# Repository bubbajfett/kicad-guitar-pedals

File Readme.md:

# Current guitar pedal projects 

Current count of pedals in this repo is something like 50.    Not doing too many more, though I have a FV-1 and a Daisy seed one I'm working on longer term, as well as clearing out the box of shame.  I have been stymied on a number of recent pedal builds testing out of box due to the rig I was using having some kind of bad wires, causing huge amounts of hum.    I reworked the testing rig and have now verified about 6 or 7 more in last week.

Anyway, the requirements here are KICAD 7 or later.     Each subdir has a gerbers directory, which has the final set of gerbers used.    

The latest change is to add a PDF in the root of each pedal directory, which has the readme, the schematic as an image, and the front and back layout of the PCB (F.Cu+F.Silkscreen, B.Cu+F.Silkscreen). Also a BOM of the parts is included.    This was all done scripted using kicad-cli  in a VM (Fedora 44, Kicad 10 !!!) as the Kicad 7 versions of this did not work very well.   I will add pics of the real tested boards as an addendum to these.    This change was a result of some feedback I recieved about the lack of clarity of what is in this repo.

These pedals have been a learning exercise for me in KiCad. Any guitar pedal PCB published here has been built and tested. In some cases, more than two versions of boards have been created.   The worst case was 5 versions.

The main idea for doing my own PCB is to allow me to change the footprints and merge and/or hack pedal schematics to come up with new ideas.
The other reason is I am redoing my pedalboard to convert from side-jacks/veroboard layout to  top-jacks/pcbs.   I have gotten to dislike veroboard layouts.

I am an amateur in this.   Also this has been a huge learning exercise.    I've tried to be consistent with some design decisions.

*   back of board mounted POTs.   Tried using both 16mm and 9mm pots (RK97?)
*   common format pinheader so to be able to use 4pin dupont connector or JST connector when building.   The topjacks pcb broke this "common format (9v, Out, In, Gnd --- from left to right)",
in that it was initially intended that the PCB be oriented closest to the the 125B shell bottom, but that made assembly more difficult.   I ordered panels of it from JLPCB, and so I;m just wiring them
backwards.
*   power on the top jack connector, with diode protection there.
*   led on the stomp switch
*   125B form factor.    Top jacks in a 1590B is really hard unless the power connector is modified or moved somewhere else.

One thing I have learned is that the text size on some of these boards is below
the JLPCB minimum recommended size; the text looks fine in osh-park boards.

Several of the build docs have pictures of the final builds.    Tonemachine is the latest...

Putting these pedal layouts out there for any interested party.   Do what you want with them. 

Here are the current repo contents.   These have all been tested outside the box,
and multiple have been successfully boxed.  12  have been boxed and are 
now on the pedalboard. 

| PEDAL | BUILD DOC | Verified|
| ----  | -------   | ------- |
| Delay/deep_blue_delay | [deep-blue-delay](./Delay/deep_blue_delay/deep_blue_delay.pdf) | Y |
| Util/stomp-chargepump |  [stomp-chargepump](./Util/stomp-chargepump/stomp-chargepump.pdf) | Y |
| Util/stomp-3pdt | [stomp-3pdt](./Util/stomp-3pdt/stomp-3pdt.pdf) | Y | 
| Util/top-jacks | [top-jacks](./Util/top-jacks/top-jacks.pdf) | Y |
| Distortion/900fuzz | [900fuzz](./Distortion/900fuzz/900fuzz.pdf) | Y |
| Distortion/acapulcogold | [acapulcogold](./Distortion/acapulcogold/acapulcogold.pdf) | Y |
| Distortion/bigmuff | [bigmuff](./Distortion/bigmuff/bigmuff.pdf) | Y | 
| Distortion/bigmuff/bmp-ramshead  | --- | Y |
| Distortion/blackdarling | --- | Y |
| Distortion/brutalistjr | [brutalist jr](./Distortion/brutalistjr/brutalistjr.pdf) | Y |
| Distortion/bmp2 | [BMP2](./Distortion/bmp2/bmp2.pdf) | Y |
| Distortion/ejfuzzface | [ejfuzzface](./Distortion/ejfuzzface/ejfuzzface.pdf) | Y |
| Distortion/fortinfuzz | [fortinfuzz](./Distortion/fortinfuzz/fortinfuzz.pdf) | Y |
| Distortion/fuzzface | [fuzzface](./Distortion/fuzzface/fuzzface.pdf) | Y |
| Distortion/fy2 | [Shin-ey fy2](./Distortion/fy2/fy2.pdf) | Y  |
| Distortion/lizardq | [lizardq](./Distortion/lizardq/lizardq.pdf) | Y | 
| Distortion/percolator | [percolator](./Distortion/percolator/percolator.pdf) | Y |
| Distortion/tonemachine | [tonemachine](./Distortion/tonemachine/tonemachine.pdf) | Y |
| Distortion/redllama | [redllama](./Distortion/redllama/redllama.pdf) | Y |
| Distortion/whitefuzz | [whitefuzz](./Distortion/whitefuzz/whitefuzz.pdf) | Y |
| Compressor/bearhug | [bearhug](./Compressor/bearhug/bearhug.pdf) | Y | 
| Compressor/engineers_thumb | [engineers_thumb](./Compressor/engineers_thumb/engineers_thumb.pdf) | Y |
| Compressor/dynacomp | ---  | Maybe? |
| Compressor/dynacomp-lm13700  | --- | N |
| Chorus/littleangel | [littleangel](./Chorus/littleangel/littleangel.pdf) | Y |
| Envelope/mutron | [mutron-v](./Envelope/mutron/mutron.pdf) | Y |
| Overdrive/SFTii | [sftii](./Overdrive/SFTii/SFTii.pdf) | Y | 
| Overdrive/triple_wreck | [triple_wreck](./Overdrive/triple_wreck/triple_wreck.pdf) | Y | 
| Overdrive/ecstacy | [ecstacy](./Overdrive/ecstacy/ecstacy.pdf) | Y | 
| Overdrive/badmonkey | [badmonkey](./Overdrive/badmonkey/badmonkey.pdf) | Y |
| Overdrive/bsiab |  [bsiab](./Overdrive/bsiab/bsiab.pdf) | Y |
| Overdrive/fatdrive | [fatdrive](./Overdrive/fatdrive/fatdrive.pdf)| Y |
| Overdrive/tweed57 | [tweed57](./Overdrive/tweed57/tweed57.pdf)|Y|
| Overdrive/timmy  | [timmy](./Overdrive/timmy/timmy.pdf) | Y |
| Overdrive/KoT | [KoT](./Overdrive/KoT/KoT.pdf) | Y | 
| Overdrive/ocd | [ocd](./Overdrive/ocd/ocd.pdf) | Y |
| Overdrive/revv-g4 | [revv-g4](./Overdrive/revv-g4/revv-g4.pdf) | Y |
| Overdrive/drboogie | ... | Y |
| Overdrive/umble | [umble](./Overdrive/umble/umble.pdf) | Y |
| Equalizer/eq | [eq](./Equalizer/eq/eq.pdf) | Y | 

PCB builds in progress are

*   Barbershop (redo)
*   paisley
*   plexidrive
*   beod

*   Klon
*   phase45
*   g2
*   bluesdriver
*   katzenkonig
*   sabbracadabra
*   tubescreamer

And 4 are stuck in the box of shame 
*   zombiechorus (9 months non-working...)
*   causalty4 phaser  (ugggh ... so close)
*   box of metal      
*   kraken

All the above subprojects have a gerbers/ subdir with the last gerber file I generated. Using OshPark for pcb generation.    They were done with Kicad 7.
Most were done with manual placement of the elements on the PCB, and then using freerouting to autoroute the traces.

License is the general Creative Commons.     Have fun!

All registered trademarks are owned by their respective owners.

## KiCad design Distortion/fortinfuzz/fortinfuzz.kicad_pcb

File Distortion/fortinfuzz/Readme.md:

# Fortin Fuzz

This is a clone of the Fortin Fuzz by fortin Amps.

The Fortin Fuzz has a very heavy doom, sludge, and drone tones.

The schematic is based on the 410 Fuzz by Pedal PCB.

All trademarks belong to their respective owners.

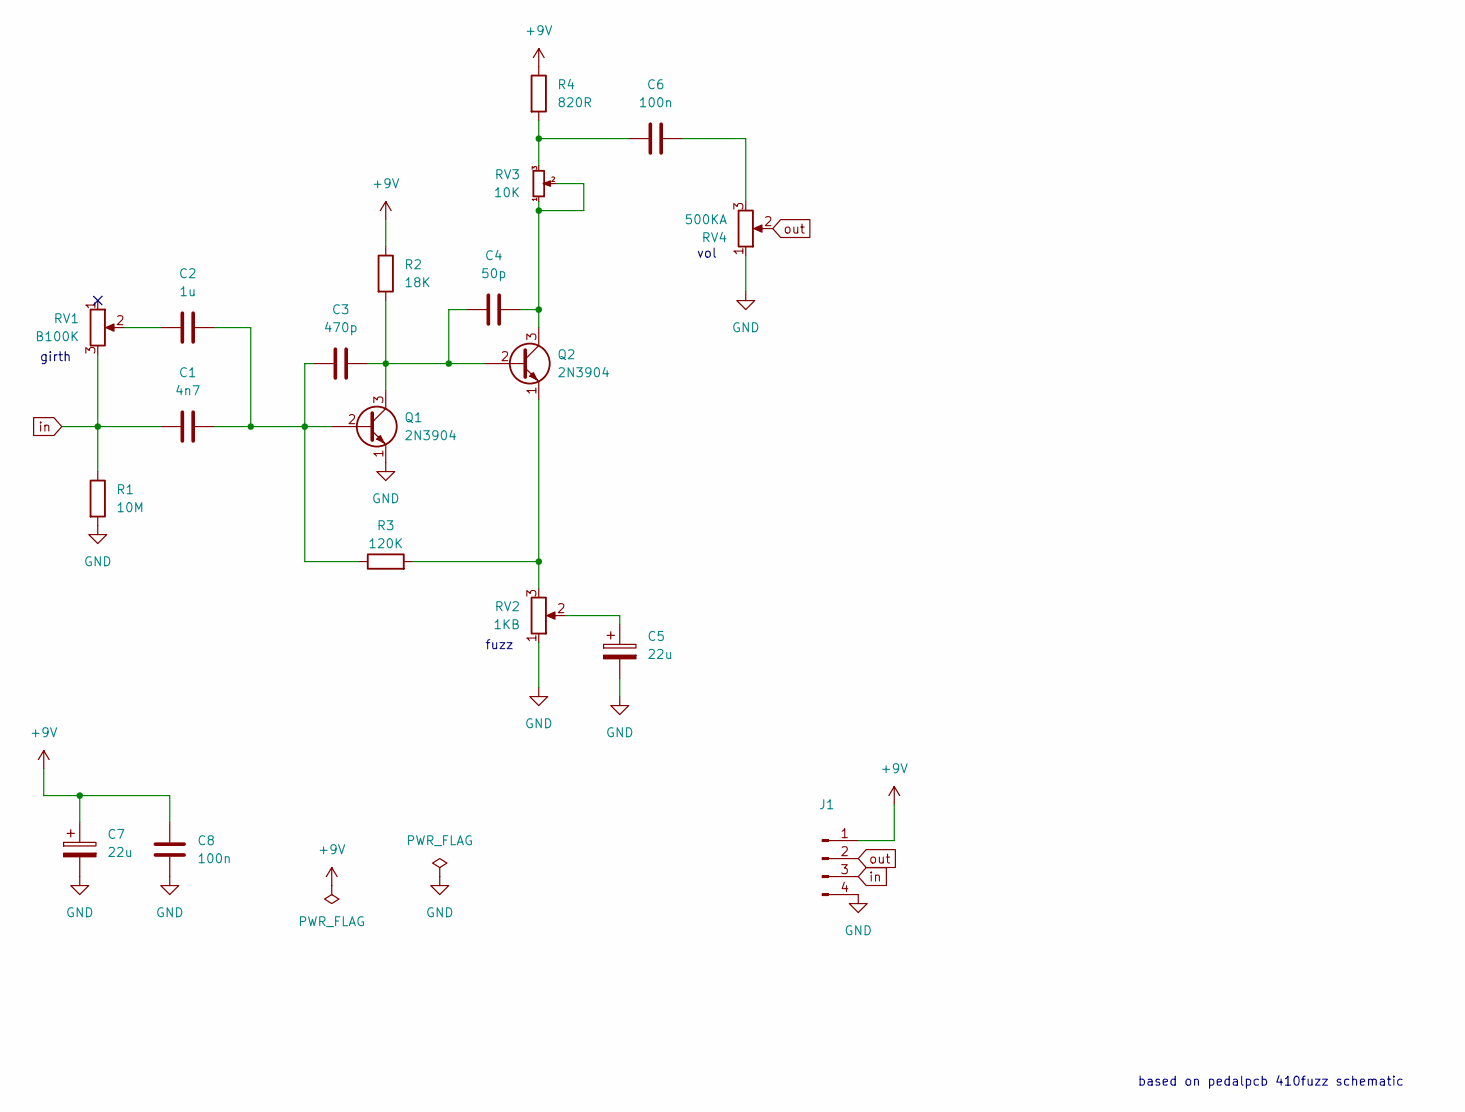
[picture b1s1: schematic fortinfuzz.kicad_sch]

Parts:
C1: 4n7; C_Rect_L7.0mm_W2.0mm_P5.00mm
C2: 1u; C_Rect_L7.0mm_W3.5mm_P5.00mm
C3: 470p; C_Rect_L7.0mm_W2.0mm_P5.00mm
C4: 50p; C_Rect_L7.0mm_W2.0mm_P5.00mm
C5, C7: 22u; CP_Radial_D5.0mm_P2.00mm
C6: 100n; C_Rect_L7.0mm_W3.5mm_P5.00mm
C8: 100n; C_Rect_L7.0mm_W2.5mm_P5.00mm
J1: Conn_01x04_Pin; PinSocket_1x04_P2.54mm_Vertical
Q1, Q2: 2N3904; TO-92_Inline
R1: 10M; R_Axial_DIN0207_L6.3mm_D2.5mm_P10.16mm_Horizontal
R2: 18K; R_Axial_DIN0207_L6.3mm_D2.5mm_P10.16mm_Horizontal
R3: 120K; R_Axial_DIN0207_L6.3mm_D2.5mm_P10.16mm_Horizontal
R4: 820R; R_Axial_DIN0207_L6.3mm_D2.5mm_P10.16mm_Horizontal
RV1: B100K; Pot_Underside
RV2: 1KB; Pot_Underside
RV3: 10K; Potentiometer_Runtron_RM-065_Vertical
RV4: 500KA; Pot_Underside

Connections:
+9V: C7.1, C8.2, J1.1, R2.1, R4.1
GND: C5.2, C7.2, C8.1, J1.4, Q1.1 (E), R1.2, RV2.1, RV4.1
unnamed: C2.1, RV1.2
unnamed: C5.1, RV2.2
unnamed: C6.1, R4.2, RV3.3
unnamed: C6.2, RV4.3
unnamed: C1.2, C2.2, C3.1, Q1.2 (B), R3.1
unnamed: C3.2, C4.1, Q1.3 (C), Q2.2 (B), R2.2
unnamed: C4.2, Q2.3 (C), RV3.1, RV3.2
unnamed: Q2.1 (E), R3.2, RV2.3
in: C1.1, J1.3, R1.1, RV1.3
out: J1.2, RV4.2

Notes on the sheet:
based on pedalpcb 410fuzz schematic
girth
fuzz
vol

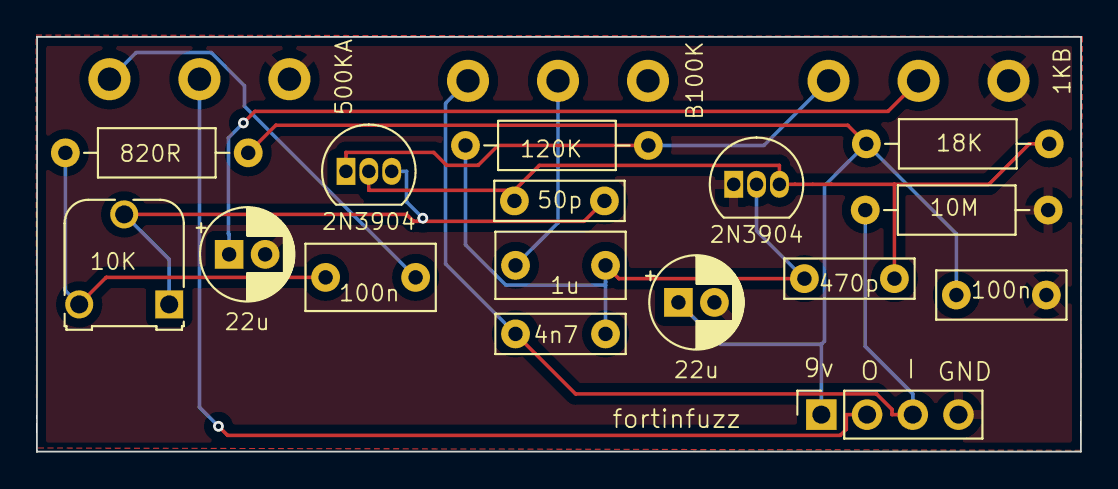
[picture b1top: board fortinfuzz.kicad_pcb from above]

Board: 2 copper layers, 58.0 x 23.0 mm, 19 parts (0 on the bottom side), 12 nets.

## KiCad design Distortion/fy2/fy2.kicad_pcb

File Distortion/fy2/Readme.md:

# Shin-ei Companion FY-2

This is a clone of the FY2 pedal, which is a very old fuzz pedal.
This produces a very thick sound. 

So this pedal circuit  is verified.  I hate using a 125B box on something
this small but my last attempt at boxing top-jacks on a
1590B did not work very well.

Anyway, all trademarks belong to their respective owners.

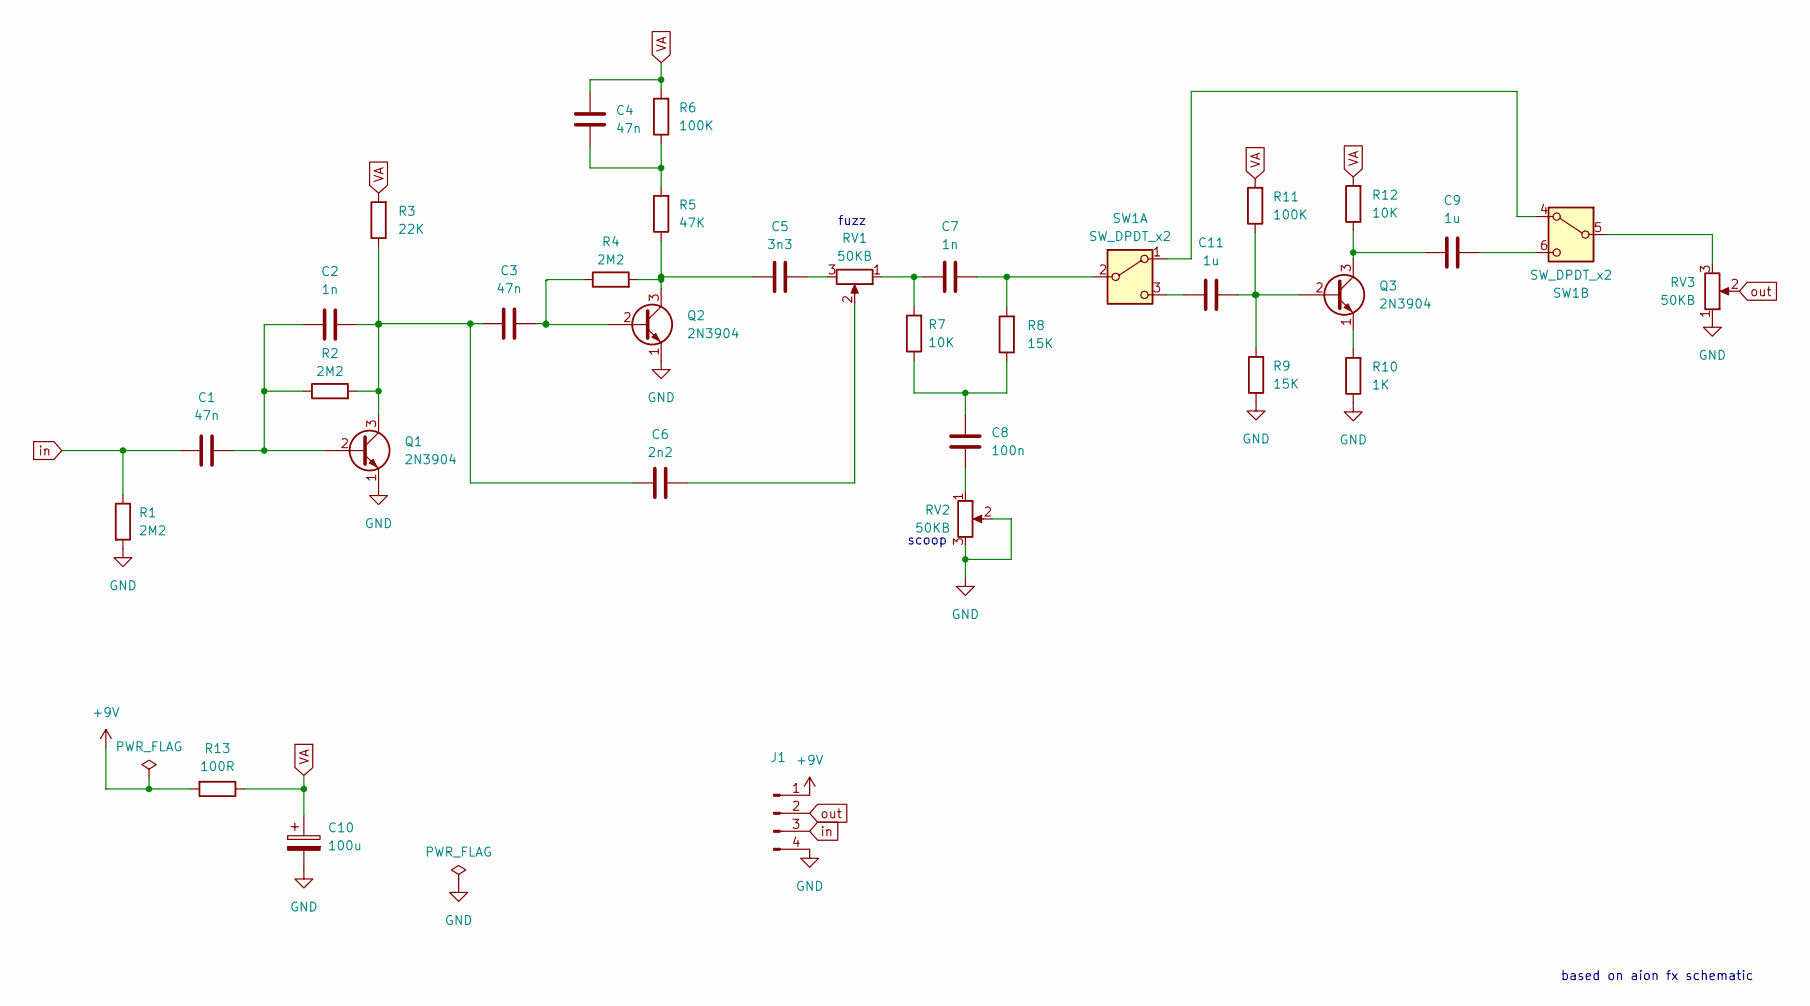
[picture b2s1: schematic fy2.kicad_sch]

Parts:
C1, C3, C4: 47n; C_Rect_L7.0mm_W2.0mm_P5.00mm
C2, C7: 1n; C_Rect_L7.0mm_W2.0mm_P5.00mm
C5: 3n3; C_Rect_L7.0mm_W2.0mm_P5.00mm
C6: 2n2; C_Rect_L7.0mm_W2.0mm_P5.00mm
C8: 100n; C_Rect_L7.0mm_W2.0mm_P5.00mm
C9, C11: 1u; C_Rect_L7.0mm_W3.5mm_P5.00mm
C10: 100u; CP_Radial_D7.5mm_P2.50mm
J1: Conn_01x04_Pin; PinSocket_1x04_P2.54mm_Vertical
Q1, Q2, Q3: 2N3904; TO-92_Inline
R1, R2, R4: 2M2; R_Axial_DIN0207_L6.3mm_D2.5mm_P10.16mm_Horizontal
R3: 22K; R_Axial_DIN0207_L6.3mm_D2.5mm_P10.16mm_Horizontal
R5: 47K; R_Axial_DIN0207_L6.3mm_D2.5mm_P10.16mm_Horizontal
R6, R11: 100K; R_Axial_DIN0207_L6.3mm_D2.5mm_P10.16mm_Horizontal
R7, R12: 10K; R_Axial_DIN0207_L6.3mm_D2.5mm_P10.16mm_Horizontal
R8, R9: 15K; R_Axial_DIN0207_L6.3mm_D2.5mm_P10.16mm_Horizontal
R10: 1K; R_Axial_DIN0207_L6.3mm_D2.5mm_P10.16mm_Horizontal
R13: 100R; R_Axial_DIN0207_L6.3mm_D2.5mm_P10.16mm_Horizontal
RV1, RV2, RV3: 50KB; Pot_Underside
SW1: SW_DPDT_x2; SWITCH-M1-DPDT

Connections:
+9V: J1.1, R13.2
GND: C10.2, J1.4, Q1.1 (E), Q2.1 (E), R1.2, R9.1, R10.1, RV2.2, RV2.3, RV3.1
unnamed: C4.1, R5.2, R6.1
unnamed: C5.2, RV1.3
unnamed: C6.2, RV1.2
unnamed: C7.1, R7.2, RV1.1
unnamed: C8.1, RV2.1
unnamed: C8.2, R7.1, R8.1
unnamed: C1.2, C2.1, Q1.2 (B), R2.1
unnamed: C2.2, C3.1, C6.1, Q1.3 (C), R2.2, R3.1
unnamed: C3.2, Q2.2 (B), R4.1
unnamed: C5.1, Q2.3 (C), R4.2, R5.1
unnamed: C11.2, Q3.2 (B), R9.2, R11.1
unnamed: C9.1, Q3.3 (C), R12.1
unnamed: Q3.1 (E), R10.2
unnamed: SW1.1 (A), SW1.4 (A)
unnamed: C7.2, R8.2, SW1.2 (B)
unnamed: C11.1, SW1.3 (C)
unnamed: RV3.3, SW1.5 (B)
unnamed: C9.2, SW1.6 (C)
VA: C4.2, C10.1, R3.2, R6.2, R11.2, R12.2, R13.1
in: C1.1, J1.3, R1.1
out: J1.2, RV3.2

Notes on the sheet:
scoop
fuzz
based on aion fx schematic

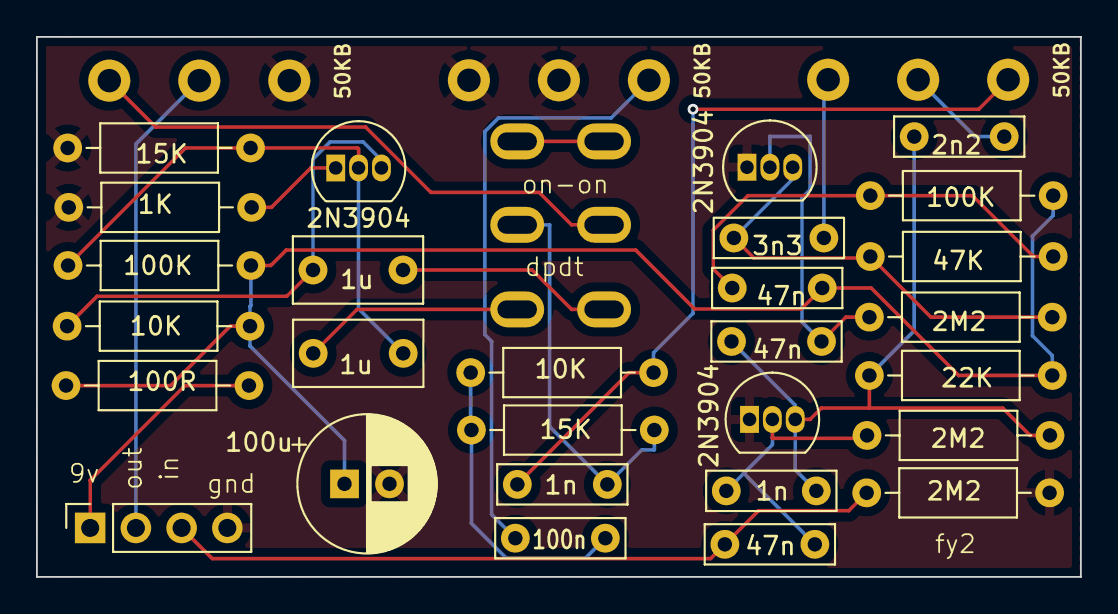
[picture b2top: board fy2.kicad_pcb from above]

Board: 2 copper layers, 58.0 x 30.0 mm, 32 parts (0 on the bottom side), 23 nets.

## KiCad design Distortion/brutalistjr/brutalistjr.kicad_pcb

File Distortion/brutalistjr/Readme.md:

# brutalist jr

This is a clone of the Brutalist JR by GOd CIty Instruments.

A very very nice distortion.   This will definitely get boxed up.

All trademarks belong to their respective owners.

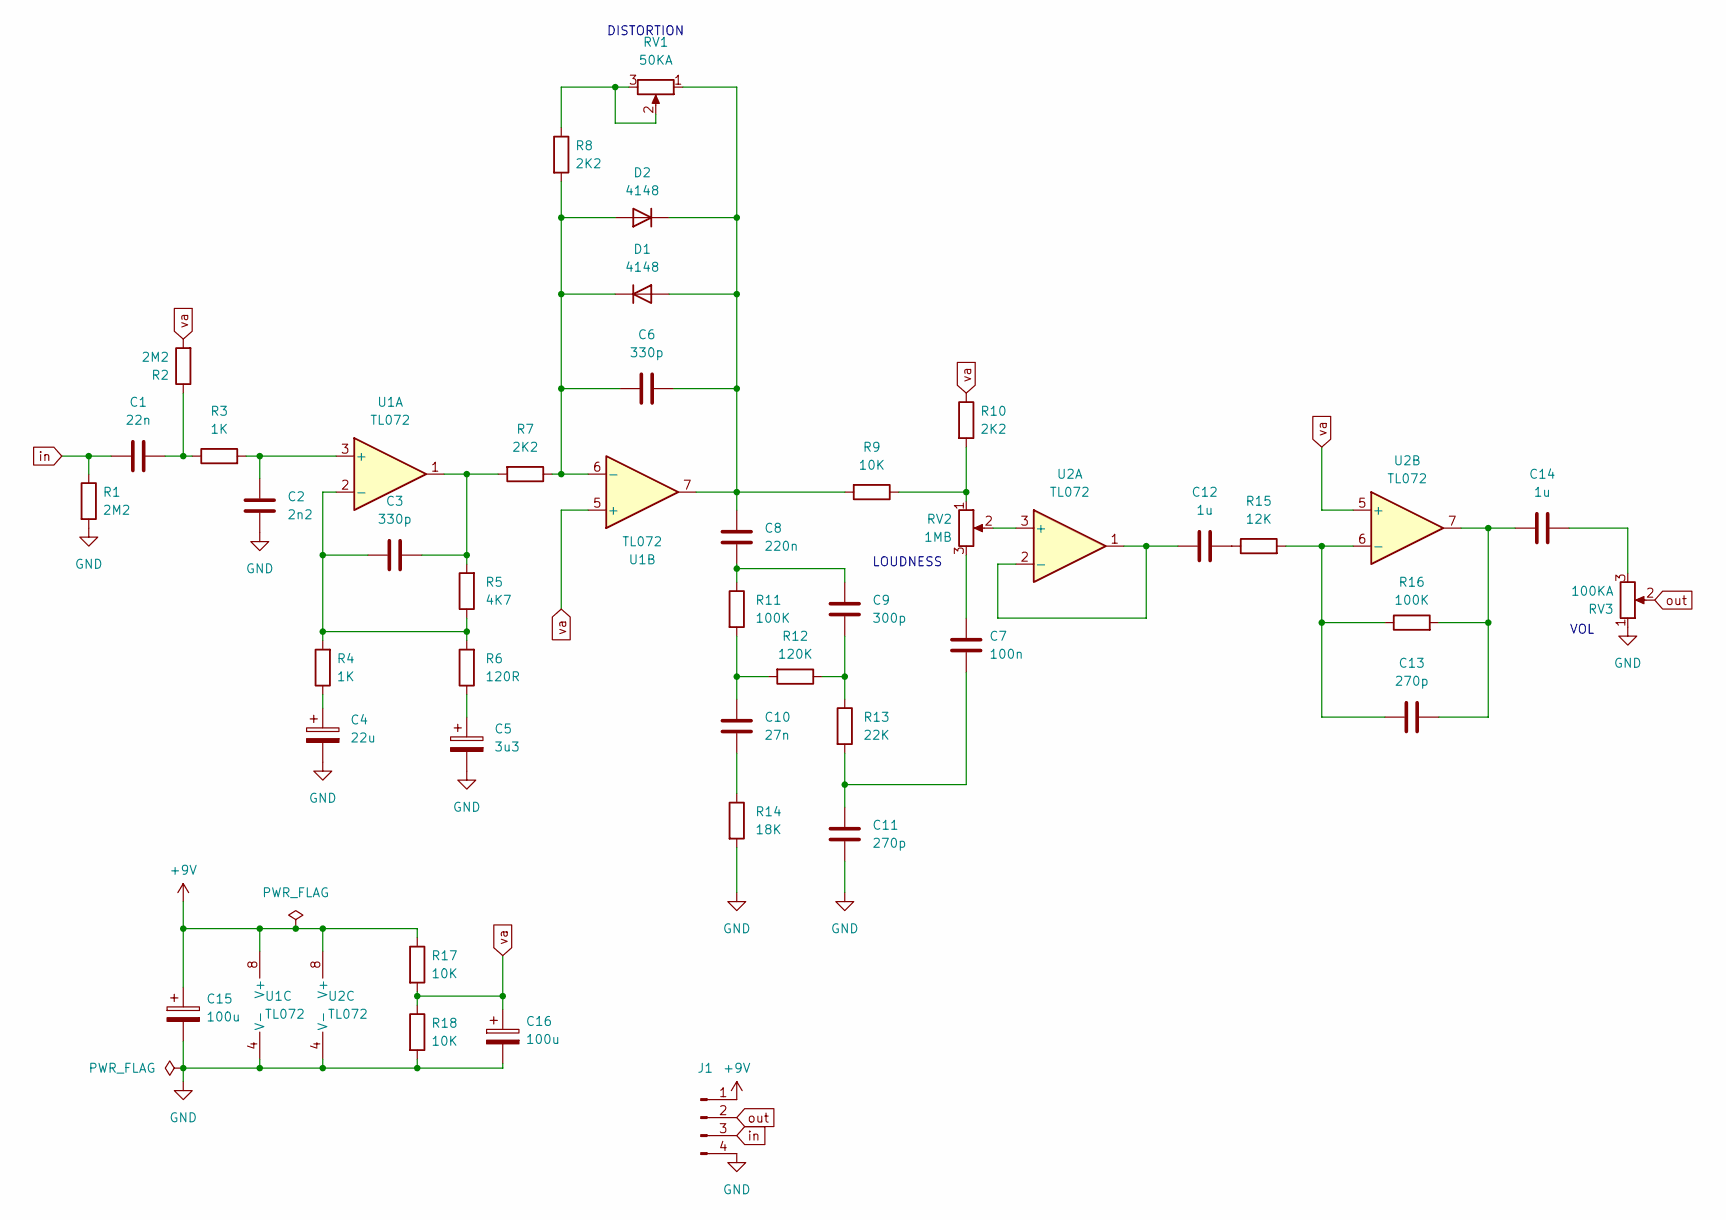
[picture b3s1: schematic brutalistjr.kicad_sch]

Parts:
C1: 22n; C_Rect_L7.0mm_W2.0mm_P5.00mm
C2: 2n2; C_Rect_L7.0mm_W2.0mm_P5.00mm
C3, C6: 330p; C_Disc_D4.3mm_W1.9mm_P5.00mm
C4: 22u; CP_Radial_D5.0mm_P2.00mm
C5: 3u3; CP_Radial_D5.0mm_P2.00mm
C7: 100n; C_Rect_L7.0mm_W2.5mm_P5.00mm
C8: 220n; C_Rect_L7.0mm_W2.5mm_P5.00mm
C9: 300p; C_Disc_D4.3mm_W1.9mm_P5.00mm
C10: 27n; C_Rect_L7.0mm_W2.0mm_P5.00mm
C11, C13: 270p; C_Disc_D4.3mm_W1.9mm_P5.00mm
C12, C14: 1u; C_Rect_L7.0mm_W2.5mm_P5.00mm
C15, C16: 100u; CP_Radial_D6.3mm_P2.50mm
D1, D2: 4148; D_DO-34_SOD68_P7.62mm_Horizontal
J1: Conn_01x04_Pin; PinHeader_1x04_P2.54mm_Vertical
R1, R2: 2M2; R_Axial_DIN0207_L6.3mm_D2.5mm_P10.16mm_Horizontal
R3, R4: 1K; R_Axial_DIN0207_L6.3mm_D2.5mm_P10.16mm_Horizontal
R5: 4K7; R_Axial_DIN0207_L6.3mm_D2.5mm_P10.16mm_Horizontal
R6: 120R; R_Axial_DIN0207_L6.3mm_D2.5mm_P10.16mm_Horizontal
R7, R8, R10: 2K2; R_Axial_DIN0207_L6.3mm_D2.5mm_P10.16mm_Horizontal
R9, R17, R18: 10K; R_Axial_DIN0207_L6.3mm_D2.5mm_P10.16mm_Horizontal
R11, R16: 100K; R_Axial_DIN0207_L6.3mm_D2.5mm_P10.16mm_Horizontal
R12: 120K; R_Axial_DIN0207_L6.3mm_D2.5mm_P10.16mm_Horizontal
R13: 22K; R_Axial_DIN0207_L6.3mm_D2.5mm_P10.16mm_Horizontal
R14: 18K; R_Axial_DIN0207_L6.3mm_D2.5mm_P10.16mm_Horizontal
R15: 12K; R_Axial_DIN0207_L6.3mm_D2.5mm_P10.16mm_Horizontal
RV1: 50KA; Pot_Underside
RV2: 1MB; Pot_Underside
RV3: 100KA; Pot_Underside
U1, U2: TL072; DIP-8_W7.62mm

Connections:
+9V: C15.1, J1.1, R17.1, U1.8 (V+), U2.8 (V+)
GND: C2.1, C4.2, C5.2, C11.1, C15.2, C16.2, J1.4, R1.2, R14.2, R18.2, RV3.1, U1.4 (V-), U2.4 (V-)
unnamed: C1.2, R2.1, R3.1
unnamed: C3.2, R5.2, R7.2, U1.1
unnamed: C4.1, R4.1
unnamed: C5.1, R6.1
unnamed: C7.2, RV2.3
unnamed: C8.1, C9.2, R11.1
unnamed: C9.1, R12.1, R13.1
unnamed: C10.1, R14.1
unnamed: C10.2, R11.2, R12.2
unnamed: C7.1, C11.2, R13.2
unnamed: C12.1, R15.1
unnamed: C13.1, C14.2, R16.2, U2.7
unnamed: C14.1, RV3.3
unnamed: C6.2, C8.2, D1.2 (A), D2.1 (K), R9.2, RV1.1, U1.7
unnamed: C6.1, D1.1 (K), D2.2 (A), R7.1, R8.2, U1.6 (-)
unnamed: R8.1, RV1.2, RV1.3
unnamed: R9.1, R10.2, RV2.1
unnamed: C2.2, R3.2, U1.3 (+)
unnamed: C3.1, R4.2, R5.1, R6.2, U1.2 (-)
unnamed: RV2.2, U2.3 (+)
unnamed: C12.2, U2.1, U2.2 (-)
unnamed: C13.2, R15.2, R16.1, U2.6 (-)
in: C1.1, J1.3, R1.1
out: J1.2, RV3.2
va: C16.1, R2.2, R10.1, R17.2, R18.1, U1.5 (+), U2.5 (+)

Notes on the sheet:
LOUDNESS
DISTORTION
VOL

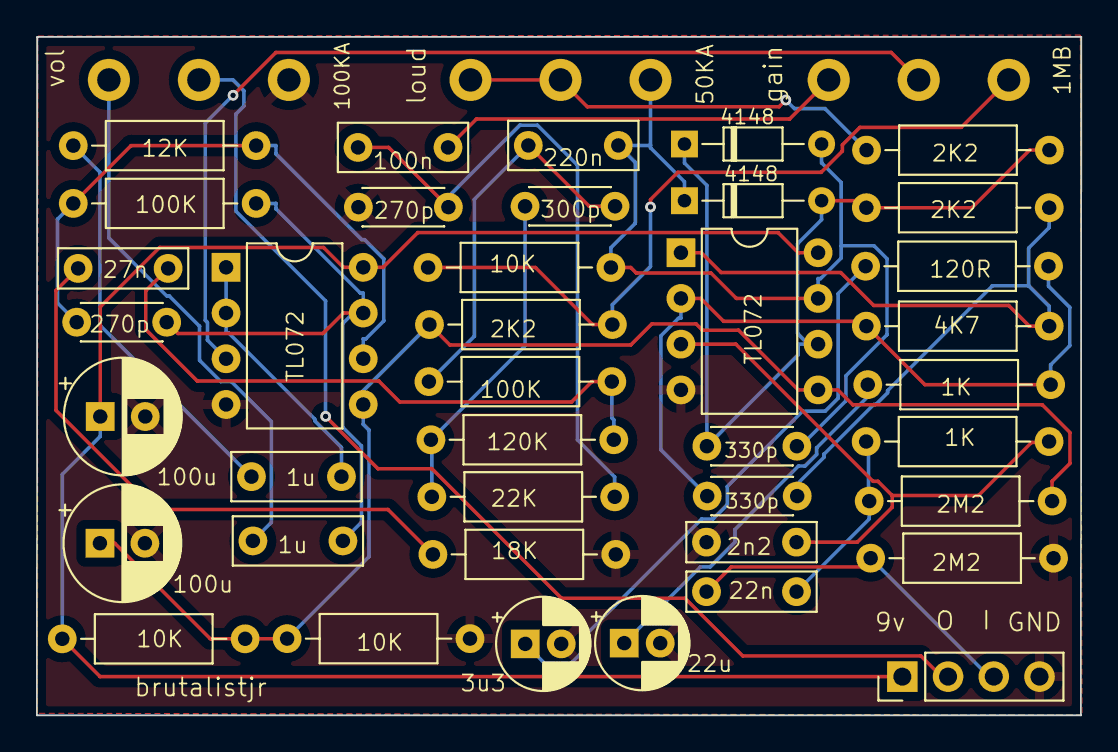
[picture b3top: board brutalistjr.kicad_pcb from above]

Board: 2 copper layers, 58.0 x 37.7 mm, 42 parts (0 on the bottom side), 27 nets.

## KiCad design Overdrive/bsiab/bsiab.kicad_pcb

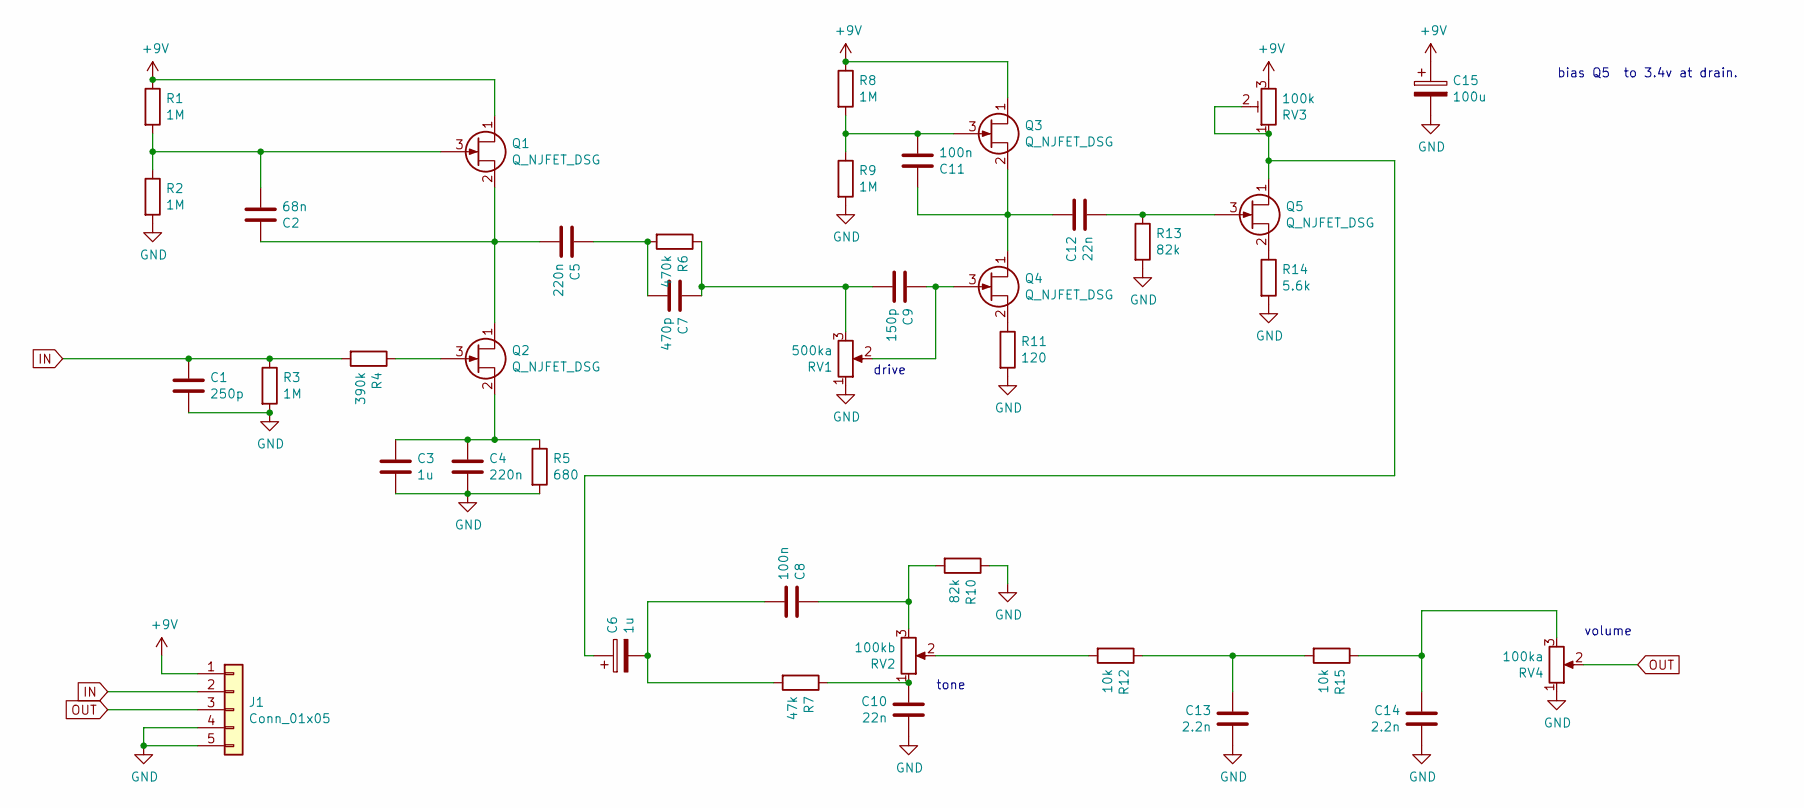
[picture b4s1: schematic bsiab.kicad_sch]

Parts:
C1: 250p; C_Disc_D5.1mm_W3.2mm_P5.00mm
C2: 68n; C_Rect_L7.0mm_W3.5mm_P2.50mm_P5.00mm
C3: 1u; C_Rect_L7.0mm_W3.5mm_P2.50mm_P5.00mm
C4, C5: 220n; C_Rect_L7.0mm_W3.5mm_P2.50mm_P5.00mm
C6: 1u; CP_Radial_D6.3mm_P2.50mm
C7: 470p; C_Disc_D5.1mm_W3.2mm_P5.00mm
C8, C11: 100n; C_Rect_L7.0mm_W3.5mm_P2.50mm_P5.00mm
C9: 150p; C_Disc_D5.1mm_W3.2mm_P5.00mm
C10, C12: 22n; C_Rect_L7.0mm_W3.5mm_P2.50mm_P5.00mm
C13, C14: 2.2n; C_Rect_L7.0mm_W3.5mm_P2.50mm_P5.00mm
C15: 100u; CP_Radial_D6.3mm_P2.50mm
J1: Conn_01x05; PinHeader_1x05_P2.54mm_Vertical
Q1, Q2, Q3, Q4, Q5: Q_NJFET_DSG; TO-92
R1, R2, R3, R8, R9: 1M; R_Axial_DIN0207_L6.3mm_D2.5mm_P10.16mm_Horizontal
R4: 390k; R_Axial_DIN0207_L6.3mm_D2.5mm_P10.16mm_Horizontal
R5: 680; R_Axial_DIN0207_L6.3mm_D2.5mm_P10.16mm_Horizontal
R6: 470k; R_Axial_DIN0207_L6.3mm_D2.5mm_P10.16mm_Horizontal
R7: 47k; R_Axial_DIN0207_L6.3mm_D2.5mm_P10.16mm_Horizontal
R10, R13: 82k; R_Axial_DIN0207_L6.3mm_D2.5mm_P10.16mm_Horizontal
R11: 120; R_Axial_DIN0207_L6.3mm_D2.5mm_P10.16mm_Horizontal
R12, R15: 10k; R_Axial_DIN0207_L6.3mm_D2.5mm_P10.16mm_Horizontal
R14: 5.6k; R_Axial_DIN0207_L6.3mm_D2.5mm_P10.16mm_Horizontal
RV1: 500ka; Potentiometer_Omeg_PC16BU_Vertical
RV2: 100kb; Potentiometer_Omeg_PC16BU_Vertical
RV3: 100k; Potentiometer_Runtron_RM-065_Vertical
RV4: 100ka; Potentiometer_Omeg_PC16BU_Vertical

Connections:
+9V: C15.1, J1.1, Q1.1 (D), Q3.1 (D), R1.1, R8.1, RV3.3
GND: C1.2, C3.2, C4.2, C10.2, C13.2, C14.2, C15.2, J1.4, J1.5, R2.2, R3.2, R5.2, R9.2, R10.1, R11.2, R13.2, R14.2, RV1.1, RV4.1
IN: C1.1, J1.2, R3.1, R4.2
unnamed: C2.1, C5.2, Q1.2 (S), Q2.1 (D)
unnamed: C2.2, Q1.3 (G), R1.2, R2.1
unnamed: C3.1, C4.1, Q2.2 (S), R5.1
unnamed: C5.1, C7.2, R6.2
unnamed: C6.1, Q5.1 (D), RV3.1, RV3.2
unnamed: C6.2, C8.2, R7.2
unnamed: C7.1, C9.2, R6.1, RV1.3
unnamed: C8.1, R10.2, RV2.3
unnamed: C9.1, Q4.3 (G), RV1.2
unnamed: C10.1, R7.1, RV2.1
unnamed: C11.1, C12.1, Q3.2 (S), Q4.1 (D)
unnamed: C11.2, Q3.3 (G), R8.2, R9.1
unnamed: C12.2, Q5.3 (G), R13.1
unnamed: C13.1, R12.1, R15.2
unnamed: C14.1, R15.1, RV4.3
unnamed: Q2.3 (G), R4.1
unnamed: Q4.2 (S), R11.1
unnamed: Q5.2 (S), R14.1
unnamed: R12.2, RV2.2
OUT: J1.3, RV4.2

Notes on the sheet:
bias Q5 to 3.4v at drain.
volume
drive
tone

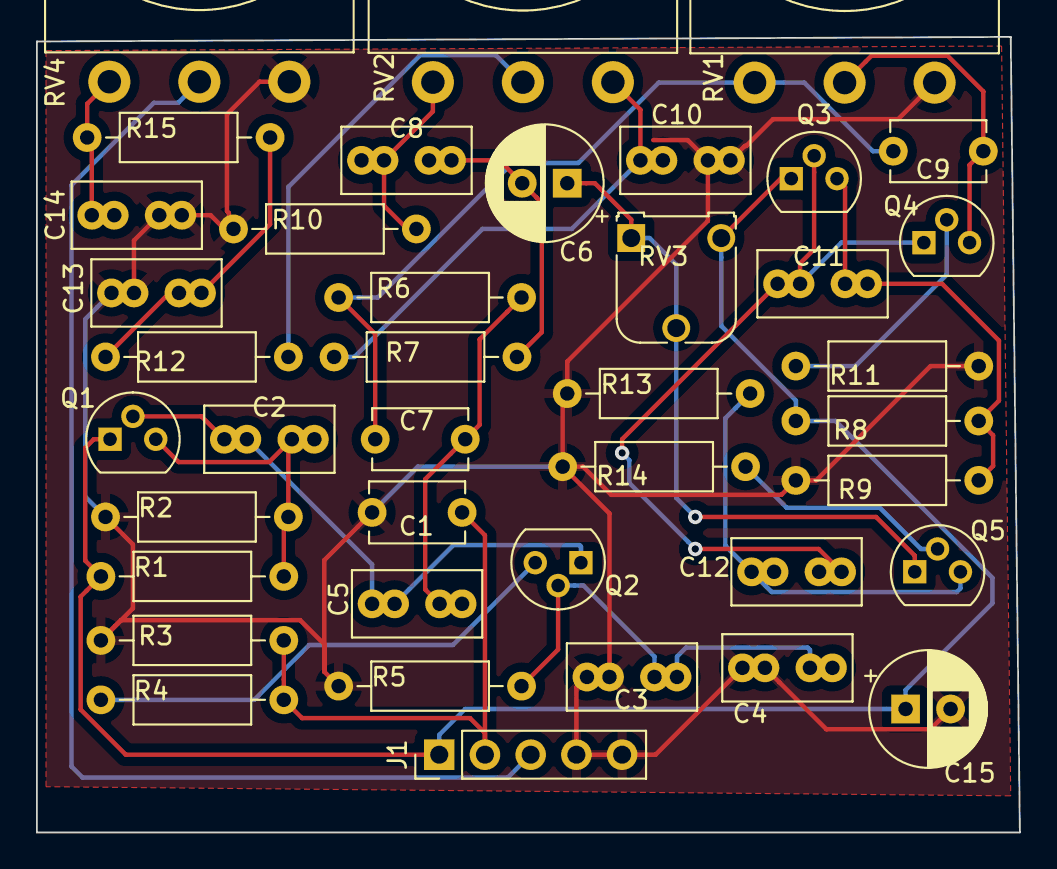
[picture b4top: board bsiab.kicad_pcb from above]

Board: 2 copper layers, 54.6 x 44.2 mm, 40 parts (0 on the bottom side), 23 nets.

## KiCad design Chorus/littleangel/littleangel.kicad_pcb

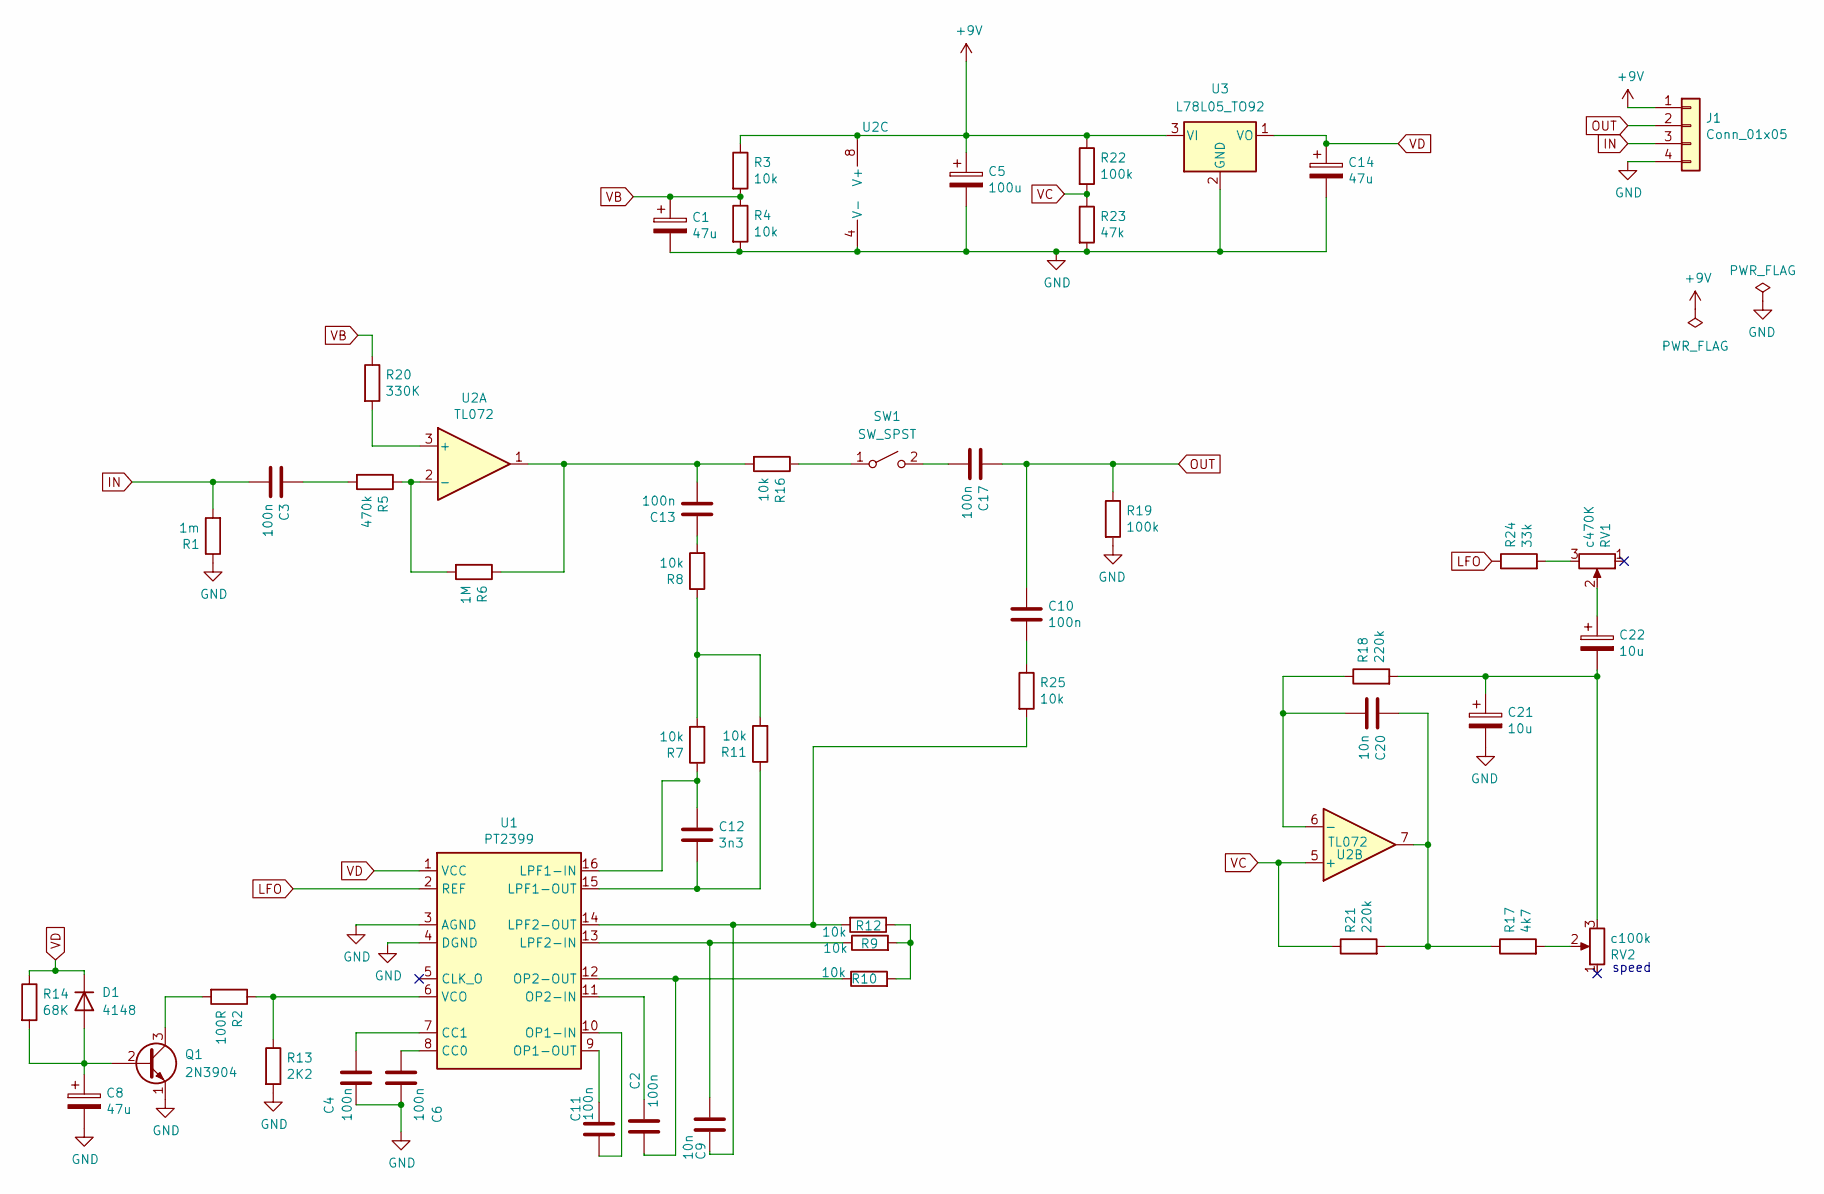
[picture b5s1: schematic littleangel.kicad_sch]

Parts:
C1, C8, C14: 47u; CP_Radial_D5.0mm_P2.00mm
C2, C3, C4, C6, C10, C11, C13, C17: 100n; C_Rect_L7.0mm_W3.5mm_P5.00mm
C5: 100u; CP_Radial_D6.3mm_P2.50mm
C9, C20: 10n; C_Rect_L7.0mm_W3.5mm_P5.00mm
C12: 3n3; C_Rect_L7.0mm_W3.5mm_P5.00mm
C21, C22: 10u; CP_Radial_D5.0mm_P2.00mm
D1: 4148; D_A-405_P7.62mm_Horizontal
J1: Conn_01x05; PinHeader_1x04_P2.54mm_Vertical
Q1: 2N3904; TO-92_Inline
R1: 1m; R_Axial_DIN0207_L6.3mm_D2.5mm_P10.16mm_Horizontal
R2: 100R; R_Axial_DIN0207_L6.3mm_D2.5mm_P10.16mm_Horizontal
R3, R4, R7, R8, R9, R10, R11, R12, R16, R25: 10k; R_Axial_DIN0207_L6.3mm_D2.5mm_P10.16mm_Horizontal
R5: 470k; R_Axial_DIN0207_L6.3mm_D2.5mm_P10.16mm_Horizontal
R6: 1M; R_Axial_DIN0207_L6.3mm_D2.5mm_P10.16mm_Horizontal
R13: 2K2; R_Axial_DIN0207_L6.3mm_D2.5mm_P10.16mm_Horizontal
R14: 68K; R_Axial_DIN0207_L6.3mm_D2.5mm_P10.16mm_Horizontal
R17: 4k7; R_Axial_DIN0207_L6.3mm_D2.5mm_P10.16mm_Horizontal
R18, R21: 220k; R_Axial_DIN0207_L6.3mm_D2.5mm_P10.16mm_Horizontal
R19, R22: 100k; R_Axial_DIN0207_L6.3mm_D2.5mm_P10.16mm_Horizontal
R20: 330K; R_Axial_DIN0207_L6.3mm_D2.5mm_P10.16mm_Horizontal
R23: 47k; R_Axial_DIN0207_L6.3mm_D2.5mm_P10.16mm_Horizontal
R24: 33k; R_Axial_DIN0207_L6.3mm_D2.5mm_P10.16mm_Horizontal
RV1: c470K; Pot_Underside
RV2: c100k; Pot_Underside
SW1: SW_SPST; SWITCH-M1-SPDT
U1: PT2399; DIP-16_W7.62mm
U2: TL072; DIP-8_W7.62mm
U3: L78L05_TO92; TO-92_Inline

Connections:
+9V: C5.1, J1.1, R3.1, R22.1, U2.8 (V+), U3.3 (VI)
GND: C1.2, C4.1, C5.2, C6.1, C8.2, C14.2, C21.2, J1.4, Q1.1 (E), R1.1, R4.2, R13.2, R19.2, R23.2, U1.3 (AGND), U1.4 (DGND), U2.4 (V-), U3.2 (GND)
IN: C3.2, J1.3, R1.2
LFO: R24.1, U1.2 (REF)
unnamed: C3.1, R5.2
unnamed: C10.2, R25.1
unnamed: C13.1, R8.2
unnamed: C13.2, R6.1, R16.2, U2.1
unnamed: C20.1, R17.1, R21.2, U2.7
unnamed: C21.1, C22.2, R18.2, RV2.3
unnamed: C22.1, RV1.2
unnamed: C8.1, D1.2 (A), Q1.2 (B), R14.2
unnamed: Q1.3 (C), R2.2
unnamed: R9.2, R10.2, R12.1
unnamed: R7.2, R8.1, R11.2
unnamed: R17.2, RV2.2
unnamed: R24.2, RV1.3
unnamed: R16.1, SW1.1 (A)
unnamed: C17.2, SW1.2 (B)
unnamed: C6.2, U1.8 (CC0)
unnamed: C4.2, U1.7 (CC1)
unnamed: C12.1, R7.1, U1.16 (LPF1-IN)
unnamed: C12.2, R11.1, U1.15 (LPF1-OUT)
unnamed: C9.1, R9.1, U1.13 (LPF2-IN)
unnamed: C9.2, R12.2, R25.2, U1.14 (LPF2-OUT)
unnamed: C11.1, U1.10 (OP1-IN)
unnamed: C11.2, U1.9 (OP1-OUT)
unnamed: C2.1, U1.11 (OP2-IN)
unnamed: C2.2, R10.1, U1.12 (OP2-OUT)
unnamed: R2.1, R13.1, U1.6 (VCO)
unnamed: R20.2, U2.3 (+)
unnamed: R5.1, R6.2, U2.2 (-)
unnamed: C20.2, R18.1, U2.6 (-)
OUT: C10.1, C17.1, J1.2, R19.1
VB: C1.1, R3.2, R4.1, R20.1
VC: R21.1, R22.2, R23.1, U2.5 (+)
VD: C14.1, D1.1 (K), R14.1, U1.1 (VCC), U3.1 (VO)

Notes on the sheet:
speed
